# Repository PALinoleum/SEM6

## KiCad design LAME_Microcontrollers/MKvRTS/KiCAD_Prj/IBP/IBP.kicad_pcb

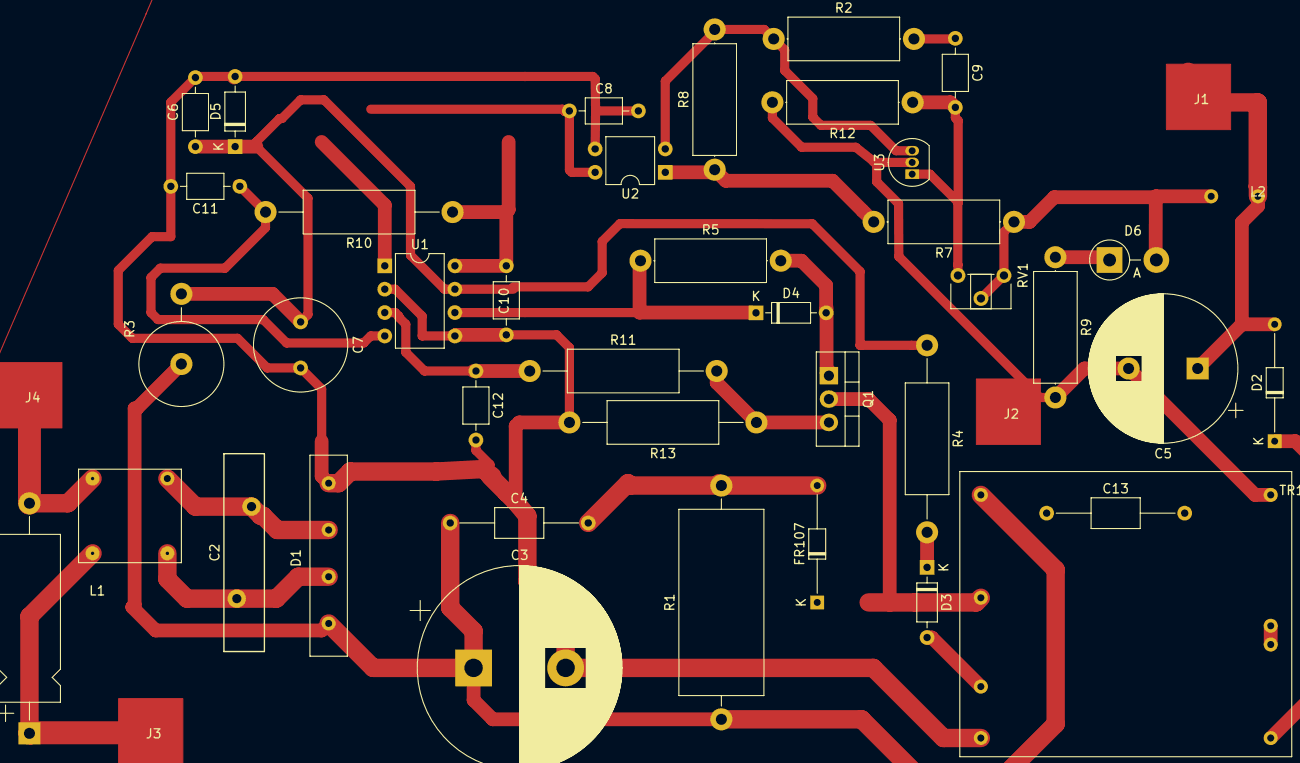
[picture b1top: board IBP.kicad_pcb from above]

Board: 2 copper layers, 44 parts (0 on the bottom side), 28 nets.

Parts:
C1: C_X; CP_Axial_L18.0mm_D6.5mm_P25.00mm_Horizontal
C2: C_Varistor; RV_Disc_D21.5mm_W4.4mm_P10mm
C3: CP; CP_Radial_D22.0mm_P10.00mm_SnapIn
C4, C13: C_4700; C_Axial_L5.1mm_D3.1mm_P15.00mm_Horizontal
C5: CP; CP_Radial_D16.0mm_P7.50mm
C6, C8, C9: C_Small; C_Axial_L3.8mm_D2.6mm_P7.50mm_Horizontal
C7: CP; C_Radial_D10.0mm_H12.5mm_P5.00mm
C10: C_100nF; C_Axial_L3.8mm_D2.6mm_P7.50mm_Horizontal
C11: C_1nF; C_Axial_L3.8mm_D2.6mm_P7.50mm_Horizontal
C12: C_0.47nF; C_Axial_L3.8mm_D2.6mm_P7.50mm_Horizontal
D1: D_Bridge_-AA+; GBU606_diodeBridge
D2: HER304; D_DO-34_SOD68_P12.70mm_Horizontal
D3, D4: 1N4148; D_DO-35_SOD27_P7.62mm_Horizontal
D5: D_Zener_27V; D_DO-35_SOD27_P7.62mm_Horizontal
D6: LED; D_5W_P5.08mm_Vertical_AnodeUp
FR107: DIODE; D_DO-34_SOD68_P12.70mm_Horizontal
J1, J2, J3, J4: Conn_01x01_Male; Pin
L1: L_Coupled; DrosselForNIR
L2: INDUCTOR; Drossel_ForNIR
Q1: IRF740; TO-220-3_Vertical
R1: R 39k; R_Axial_DIN0922_L20.0mm_D9.0mm_P25.40mm_Horizontal
R2, R5, R7, R8, R9, R12: R; R_Axial_DIN0414_L11.9mm_D4.5mm_P15.24mm_Horizontal
R3: R 300k 2W; R_Axial_DIN0918_L18.0mm_D9.0mm_P7.62mm_Vertical
R4: R 33; R_Axial_DIN0414_L11.9mm_D4.5mm_P20.32mm_Horizontal
R10, R11: R 1k; R_Axial_DIN0414_L11.9mm_D4.5mm_P20.32mm_Horizontal
R13: R 1.8; R_Axial_DIN0414_L11.9mm_D4.5mm_P20.32mm_Horizontal
RV1: R_POT_Dual_Separate; Potentiometer_ACP_CA6-H2,5_Horizontal
TR1: TRANSF6; MyIBP_ForNIR
U1: UC3843_DIP8; DIP-8_W7.62mm
U2: SFH617A-1; DIP-4_W7.62mm
U3: TL431LP; TO-92_Inline

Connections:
GNDREF: C3.2, C6.2, C7.2, C8.2, C10.2, C11.2, C12.2, D1.1, D5.2, R13.2, TR1.4, U1.2, U1.5, U2.3
unnamed: C1.1, L1.1
unnamed: C1.2, L1.3
unnamed: C2.1, D1.2, L1.2
unnamed: C2.2, D1.3, L1.4
unnamed: C3.1, C4.1, D1.4, R1.1, R3.1, TR1.1
unnamed: C4.2, FR107.2, R1.2
unnamed: C5.1, D2.2, L2.1
unnamed: C6.1, C7.1, D5.1, R3.2, R4.1, U1.7
unnamed: C8.1, U1.1, U2.4
unnamed: C9.1, R2.2
unnamed: C9.2, R12.1, RV1.3, U3.1
unnamed: C10.1, R10.1, U1.8
unnamed: C11.1, R10.2, U1.4
unnamed: C12.1, R11.1, U1.3
unnamed: C13.1, FR107.1, Q1.2, TR1.2
unnamed: C5.2, C13.2, R9.2, R12.2, TR1.5, U3.2
unnamed: D2.1, TR1.8
unnamed: D3.1, R4.2
unnamed: D3.2, TR1.3
unnamed: D4.1, R5.1, U1.6
unnamed: D4.2, Q1.1, R5.2
unnamed: D6.1, R9.1
unnamed: D6.2, L2.2, R7.1, RV1.1, RV1.2
unnamed: Q1.3, R11.2, R13.1
unnamed: R2.1, R8.2, U2.2, U3.3
unnamed: R7.2, R8.1, U2.1
unnamed: TR1.6, TR1.7

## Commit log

2020-07-08 Загрузил имеющиеся работы
